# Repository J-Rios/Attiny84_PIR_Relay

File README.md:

# Attiny84_PIR_Relay
Attiny84 based system that control a relay through a PIR sensor (with Arduino code).
[See Image of the board](Image.png).
-------------------------------------------------------------------------------------
Proceso de funcionamiento:
  1- Mira la luminosidad del ambiente.
  2- Compara la luminosidad con cierto umbral.
  3- Si todavia hay luz, se duerme durante 10 minutos, tras ello se despierta y pasa a 1.
  4- Si hay suficiente oscuridad, detecta presencia.
  5- Si hay presencia, enciende la luz y se duerme durante 1 minuto, tras ello se despierta y pasa a 1.
  6- Si no hay presencia, se apaga la luz y se duerme durante 1 segundo, tras ello se despierta y pasa a 1.
  
Habra por tanto dos modos de funcionamiento según la luminosidad:
  De dia: Duerme y se despierta cada 10 minutos para ver si se ha hecho de noche.
  De noche: Duerme y se despierta cada 1 segundo para ver si hay presencia. Si hay presencia enciende la luz y se
  espera (durmiendo) 1 minuto. Si no hay presencia apaga la luz.
  
  Nota: Al programar la posicion del interruptor hay que tenerlo en cuenta para que no este en un estado de pull
  (activado) ya que es un pin de programacion.
  
Attiny84 1MHz

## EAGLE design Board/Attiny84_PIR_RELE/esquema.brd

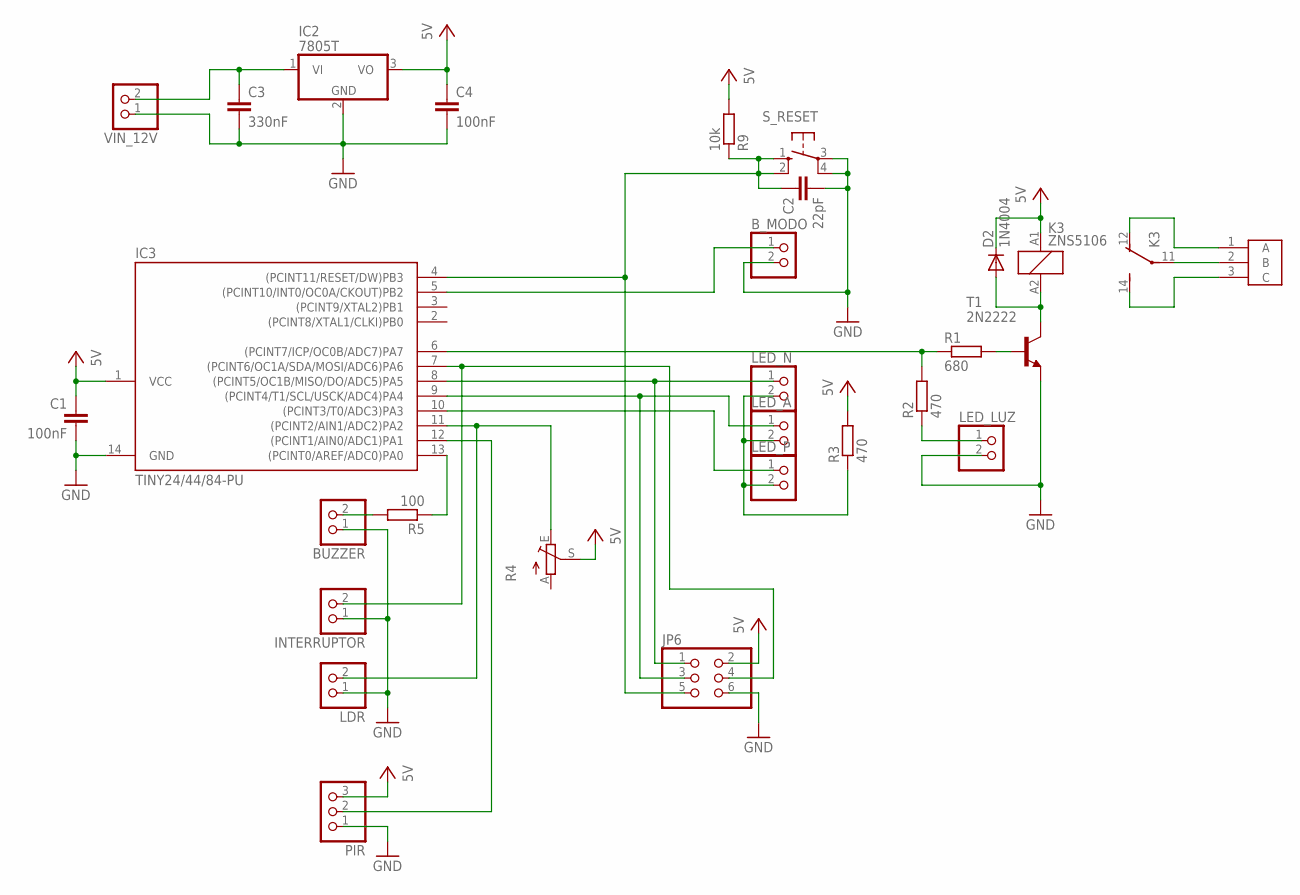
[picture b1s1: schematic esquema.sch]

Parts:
BUZZER: PINHD-1X2; 1X02
B_MODO: PINHD-1X2; 1X02
C1, C4: 100nF; C050-025X075
C2: 22pF; C050-025X075
C3: 330nF; C050-025X075
D2: 1N4004; DO41-10
IC2: 7805T; TO220H
IC3: TINY24/44/84-PU; DIL14
INTERRUPTOR: PINHD-1X2; 1X02
JP6: PINHD-2X3; 2X03
K3: ZNS5106; ZN5
LDR: PINHD-1X2; 1X02
LED_A: PINHD-1X2; 1X02
LED_LUZ: PINHD-1X2; 1X02
LED_N: PINHD-1X2; 1X02
LED_P: PINHD-1X2; 1X02
PIR: PINHD-1X3; 1X03
R1: 680; 0204/7
R2, R3: 470; 0204/7
R4: TRIM_EU-LI10; LI10
R5: 100; 0204/7
R9: 10k; 0204/7
S_RESET: 10-XX; B3F-10XX
T1: 2N2222; TO18
U$1: POT_CONNECTOR
VIN_12V: PINHD-1X2; 1X02

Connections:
GND: BUZZER.1, B_MODO.2, C1.2, C2.2, C3.2, C4.2, IC2.2 (GND), IC3.14 (GND), INTERRUPTOR.1, JP6.6, LDR.1, LED_LUZ.2, PIR.1, S_RESET.3, S_RESET.4 (P1), T1.1 (E), VIN_12V.1
MISO: IC3.8 ((PCINT5/OC1B/MISO/DO/ADC5)PA5), JP6.1, LED_N.1
unnamed: B_MODO.1, IC3.5 ((PCINT10/INT0/OC0A/CKOUT)PB2)
unnamed: IC3.7 ((PCINT6/OC1A/SDA/MOSI/ADC6)PA6), INTERRUPTOR.2, JP6.4
unnamed: IC3.11 ((PCINT2/AIN1/ADC2)PA2), LDR.2, R4.E
unnamed: IC3.10 ((PCINT3/T0/ADC3)PA3), LED_P.1
unnamed: IC3.12 ((PCINT1/AIN0/ADC1)PA1), PIR.2
unnamed: BUZZER.2, R5.2
unnamed: IC3.13 ((PCINT0/AREF/ADC0)PA0), R5.1
unnamed: C3.1, IC2.1 (VI), VIN_12V.2
unnamed: LED_A.2, LED_N.2, LED_P.2, R3.1
unnamed: K3.11, U$1.2 (B)
unnamed: D2.A, K3.A2 (2), T1.3 (C)
unnamed: R1.2, T1.2 (B)
unnamed: IC3.6 ((PCINT7/ICP/OC0B/ADC7)PA7), R1.1, R2.2
unnamed: K3.12 (O), U$1.1 (A)
unnamed: LED_LUZ.1, R2.1
unnamed: K3.14 (S), U$1.3 (C)
RESET: C2.1, IC3.4 ((PCINT11/RESET/DW)PB3), JP6.5, R9.1, S_RESET.1 (S), S_RESET.2 (S1)
SCK: IC3.9 ((PCINT4/T1/SCL/USCK/ADC4)PA4), JP6.3, LED_A.1
VCC: C1.1, C4.1, D2.C, IC2.3 (VO), IC3.1 (VCC), JP6.2, K3.A1 (1), PIR.3, R3.2, R4.S, R9.2

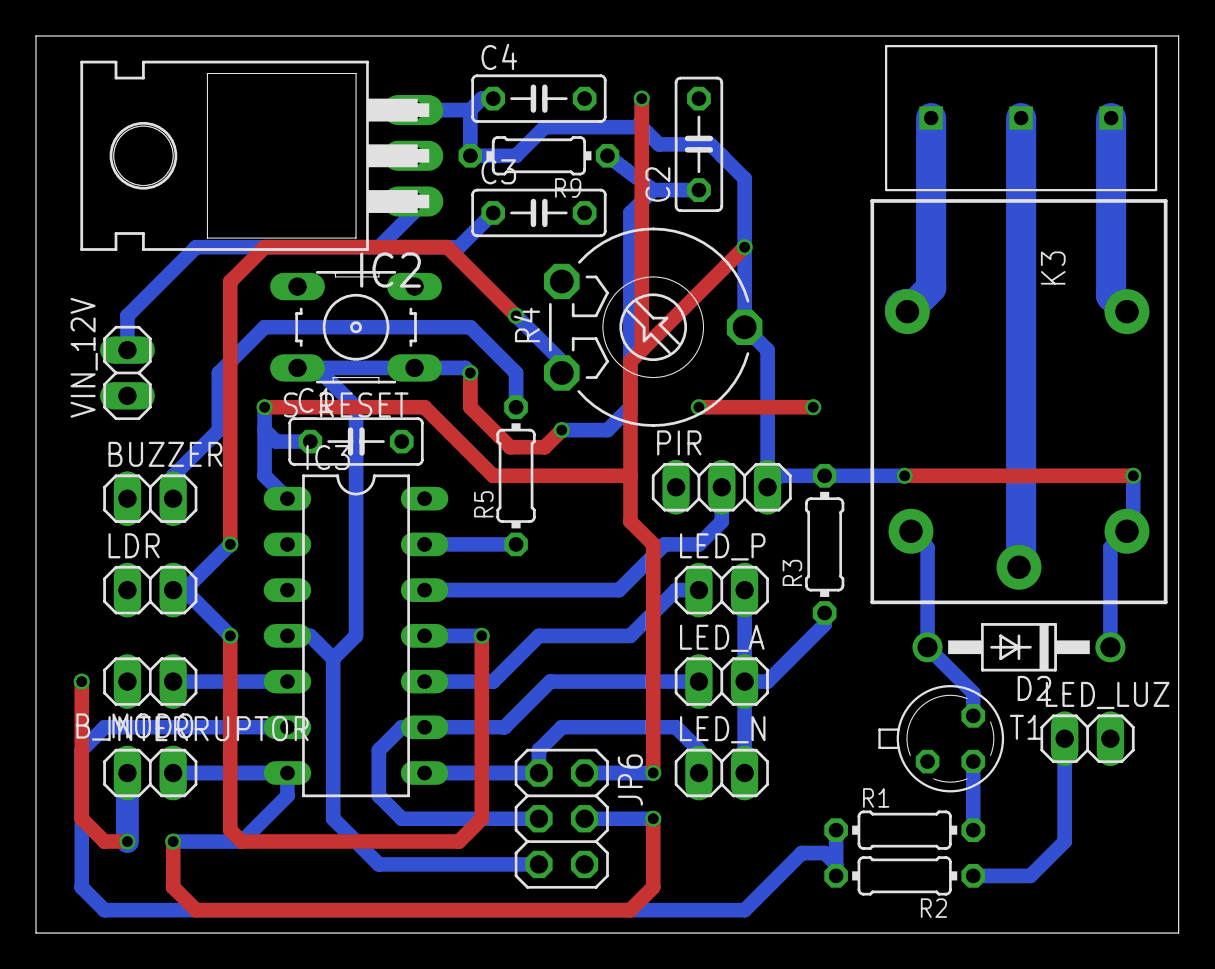
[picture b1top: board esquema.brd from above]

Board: 2 copper layers, 63.5 x 49.8 mm, 28 parts (0 on the bottom side), 21 nets.

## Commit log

2015-04-27 Code
    Arduino code
2015-04-27 Board
    Eagle Board
2015-04-27 Renombre
    Cambio de nombre de Attiny85 a Attiny84
2015-05-10 Image
    Image added
2015-05-14 Delete files
    Delete dummy files of the Eagle board project
